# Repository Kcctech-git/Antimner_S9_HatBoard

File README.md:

# Antminer S9 Control Board HAT
## Disclaimer

Following the global mining boom, large numbers of used Antminer S9 control boards have become widely available on secondary markets for as little as $5–30.
These boards, originally built to control cryptocurrency mining equipment, are based on the well-documented Xilinx Zynq-7010 (XC7Z010) SoC and include:

 - Two Arm® Cortex®-A9 processor cores

 - Gigabit Ethernet

 - 512 MB or 1 GB DDR3 RAM

 - 256 Mb SLC NAND flash

 - MicroSD card

 - Exposed PS–PL interface pins, some of which are connected to various peripherals
 
 - Supports Linux and FreeRTOS

Because of their solid hardware design and abundance, these boards make excellent low-cost development platforms for embedded Linux, RTOS, FPGA, or hardware-software co-design experiments — especially when combined with this HAT expansion board.

## Overview

This project is a KiCad-based expansion board (HAT) designed for the Antminer S9 Control Board built around the Xilinx Zynq-7010 (XC7Z010) SoC.
The board extends the original functionality of the control board by adding:

PS-side ULPI USB controller — enabling standard USB host/device connectivity via the Zynq Processing System.

HDMI output interface — connected directly to the Zynq PL (Programmable Logic) fabric for video output or diagnostics.

Breakout header exposing all remaining available PL I/O pins of the Zynq device (except 8 pins used for HDMI).

The goal of this project is to repurpose the Antminer S9 control board into a versatile FPGA development platform, enabling experimentation with Zynq PS/PL subsystems, video output, and general FPGA prototyping.

## Features

 - Compatible with Antminer S9 Zynq-7010 control boards

 - Adds USB ULPI PHY connected to the Zynq PS

 - Adds HDMI TX output using 8 PL pins for TMDS signaling

 - Breaks out all remaining PL I/O to 2.54 mm header

 - Designed in KiCad 9.0 (schematic + PCB files included)

 - Fits within the mechanical envelope of the S9 control board

### This HAT board enables multiple new use cases for the Antminer S9 Control Board:

 - Use as a Zynq FPGA development board with easy access to PL I/O

 - Implement custom video output via HDMI for FPGA or Linux framebuffer

 - Utilize USB host/device support through the PS-side ULPI PHY

 - Experiment with bare-metal or Linux projects using the onboard DDR, flash, and Ethernet

 - Perform reverse engineering, diagnostics, or educational FPGA projects on low-cost S9 boards

## Purpose of the Design

The main goal of this HAT board was to enable the built-in USB 2.0 controller inside the Zynq-7010 Processing System (PS).
Although the Zynq PS includes a native ULPI interface for USB, its signals on the Antminer S9 control board are routed to scattered locations and are not interconnected in a usable way.

This board collects all required ULPI pins from different areas of the control board, aligns their routing lengths, and connects them to a USB PHY (USB3315C).
Because the parallel ULPI bus operates at approximately 60 MHz, and the trace length on the HAT is around 16 cm — close to the reliable signaling limit — special care was taken to maintain consistent line length and impedance.

To minimize signal reflections, 30 Ω series resistors were added on all ULPI data lines.
Testing confirmed that the USB 2.0 interface operates reliably and stably: files larger than 100 MB can be read and written from a USB flash drive without errors.

## Hardware Modifications (Required)

To enable the PS-side ULPI USB interface, a few small modifications are required on the Antminer S9 Zynq-7010 Control Board.
These steps free PS MIO pins previously used by on-board peripherals and provide mechanical clearance for the HAT board.

### Steps

1. Remove Q2 and Q3
These transistors are connected to MIO lines needed for ULPI.
Removing them frees access to: PS_MIO37 and PS_MIO38

2. Wire PS_MIO37 and PS_MIO38 to J11
Solder 60 mm insulated wires from the Q2/Q3 gate pads to PS_MIO37, PS_MIO38

4. Wire PS_MIO39 to J11
Solder a 102 mm insulated wire from the resistor pad (previously tied to control logic) to PS_MIO39

6. Remove capacitors for clearance
Desolder the following mechanically blocking capacitors to allow the HAT board to seat properly C195, C197, C229

7. Connect auxiliary signals to J11 (Aux MIO Connector on HAT)
8. Hook up the freed MIO lines and power signals to the J11 header on the HAT board.
See pinout table below.

9. Provide +12 V to J12 (12 V Pwr on HAT)
10. Connect the +12 V rail from the control board to the J12 input on the HAT.
The HAT generates 5 V and 1.8 V locally for its subsystems.

### J11 (Aux MIO Connector) Pinout
|  Pin	 |  Signal   |	Direction	Notes                                        |
| ----- | --------  | ------------------------------------------------------ |
| 1	    | USB_VDD_IO| (2.5 V)	Power	I/O voltage reference for Zynq PS Bank 1 |
| 2	    | RESET     |	Input	Optional; not used in the reference build        |
| 3     |	PS_MIO39  |	I/O	ULPI signal                                        |
| 4	    | PS_MIO38  |	I/O	ULPI signal                                        |
| 5     |	PS_MIO37  |	I/O	ULPI signal                                        |

### Note: Verify pin orientation according to the silkscreen and schematic before soldering.
Keep wires short (≤ 100 mm) and add strain relief where possible.

### Result:
After completing these modifications, the HAT board’s USB3315C ULPI controller is correctly connected to the Zynq PS USB interface through PS_MIO37–39, with the proper 2.5 V I/O reference and power supplied via J12.

## Bill of Materials (BOM)

| Ref                    | Qty | Value            | Description / Notes                  | Footprint / Link                                                                                                            |
| ---------------------- | --- | ---------------- | ------------------------------------ | --------------------------------------------------------------------------------------------------------------------------- |
| **USB & Power**        |     |                  |                                      |                                                                                                                             |
| IC1                    | 1   | USB3315C-CP-TR   | ULPI USB PHY                         | [Microchip Datasheet](http://ww1.microchip.com/downloads/en/DeviceDoc/3315.pdf)                                             |
| IC2                    | 1   | LM3525M-H        | USB Power Switch                     | [TI Datasheet](https://www.ti.com/product/LM3525)                                                                           |
| J14                    | 1   | USB-C Receptacle | USB2.0 16-pin                        | [USB Type-C Spec](https://www.usb.org/sites/default/files/documents/usb_type-c.zip)                                         |
| J15                    | 1   | 48204-0001       | IO Connector (Molex type)            | [Molex 48204-0001](http://www.molex.com/webdocs/datasheets/pdf/en-us/0482040001_IO_CONNECTORS.pdf)                          |
| Y1                     | 1   | 24 MHz           | ULPI Clock Oscillator                | [Abracon ASV](http://www.abracon.com/Oscillators/ASV.pdf)                                                                   |
| **HDMI Interface**     |     |                  |                                      |                                                                                                                             |
| J13                    | 1   | HDMI Type-A      | Output Connector                     | [Molex 208658-1001](https://www.molex.com/en-us/products/part-detail/2086581001)                                            |
| D1, D6, D7             | 3   | CDDFN10-0524P    | HDMI ESD Protection                  | [Bourns CDDFN10-0524P](https://www.bourns.com/docs/Product-Datasheets/CDDFN10-0524P.pdf)                                    |
| **Voltage Regulation** |     |                  |                                      |                                                                                                                             |
| U1                     | 1   | L7805            | 5 V Linear Regulator                 | [ST L7805](https://www.st.com/resource/en/datasheet/l78.pdf)      |
| U2                     | 1   | LM1117DT-1.8     | 1.8 V Regulator                      | [TI LM1117](http://www.ti.com/lit/ds/symlink/lm1117.pdf)                                                                    |
| **Connectors**         |     |                  |                                      |                                                                                                                             |
| J1–J9                  | 9   | Conn_02x09       | PL / GPIO Headers (2 mm pitch)       | —                                                                                                                           |
| J11                    | 1   | Aux_mio_conn     | 1×5 Header 2.54 mm                   | —                                                                                                                           |
| J12                    | 1   | 12 V Pwr         | 2×2 Socket 2.54 mm                   | —                                                                                                                           |
| J16                    | 1   | PL_conn          | 1×37 Header 2.54 mm                  | —                                                                                                                           |
| **Passive Components** |     |                  |                                      |                                                                                                                             |
| C1                     | 1   | 47 µF 25 V       | Bulk decoupling                      | 1206                                                                                                                        |
| C2                     | 1   | 100 µF 10 V      | Bulk decoupling                      | 1206                                                                                                                        |
| C3                     | 1   | 100 nF           | Decoupling                           | 1206                                                                                                                        |
| C4                     | 1   | 1 nF             | Filter                               | 1206                                                                                                                        |
| C5, C6, C13, C23, C25  | 5   | 0.1 µF           | Bypass capacitors                    | 0805                                                                                                                        |
| C7                     | 1   | 100 µF           | Bulk capacitor                       | 1210                                                                                                                        |
| C8                     | 1   | 1 nF             | Filter                               | 1206                                                                                                                        |
| C14, C24               | 2   | 10 µF            | Local decoupling                     | 1206                                                                                                                        |
| R1                     | 1   | 1 MΩ             | Pull-down                            | 0805                                                                                                                        |
| R2                     | 1   | 820 Ω            | LED limiter                          | 0805                                                                                                                        |
| R3, R20                | 2   | 2 kΩ             | General pull-up                      | 0805                                                                                                                        |
| R4                     | 1   | 4.7 kΩ           | I²C pull-up                          | 0805                                                                                                                        |
| R5                     | 1   | 8.06 kΩ          | Divider                              | 0805                                                                                                                        |
| R6–R19                 | 11  | 30 Ω             | HDMI series termination              | 0805                                                                                                                        |
| R21                    | 1   | 1 MΩ             | General pull-down                    | 0805                                                                                                                        |
| RN1, RN2               | 2   | TC164-FR-0749R9L | 49.9 Ω resistor network (4×)         | [Yageo Datasheet](https://www.yageo.com/upload/media/product/productsearch/datasheet/rchip/PYu-YC_TC_group_51_RoHS_L_9.pdf) |
| D2, D8                 | 2   | LED              | Status indicators                    | Any 1206/1210 Leds                                                                                                                        |
| D4                     | 1   | 1N5822           | Schottky diode                       | [Vishay 1N5822](http://www.vishay.com/docs/88526/1n5820.pdf)                                                                |
| **Test Points**        |     |                  |                                      |                                                                                                                             |
| TP1–TP6                | 6   | —                | CEC, SCL, SDA, HPD, UTILITY, 5V_HDMI | TestPoint Ø1.5 mm                                                                                                           |

## Known Limitations

HDMI interface uses AC-coupled LVCMOS-TMDS signaling (non-standard but functional).

Voltage compatibility of some PL banks depends on existing S9 circuitry — verify I/O standards before connecting.

Power is drawn directly from the S9 board (3.3 V and 12 V rails).

## License

Licensed under CERN Open Hardware Licence v2 - Permissive (CERN-OHL-P)
SPDX-License-Identifier: CERN-OHL-P-2.0

Full license text:
https://ohwr.org/cern_ohl_p_v2.txt

## Credits

Designed by Kanstantsin Salamiyuk

Created to extend and repurpose the Antminer S9 Zynq-7010 control board as an open FPGA development platform.
KiCad design files and documentation are provided for educational and experimental use.

## Disclaimer

This project is not affiliated with or endorsed by Bitmain Technologies.
All hardware modifications and usage are performed at your own risk.
Improper connections may damage the control board or FPGA.

**Tags:** `FPGA` `Zynq-7010` `Antminer S9` `Embedded Linux` `ULPI` `HDMI` `Open Hardware`

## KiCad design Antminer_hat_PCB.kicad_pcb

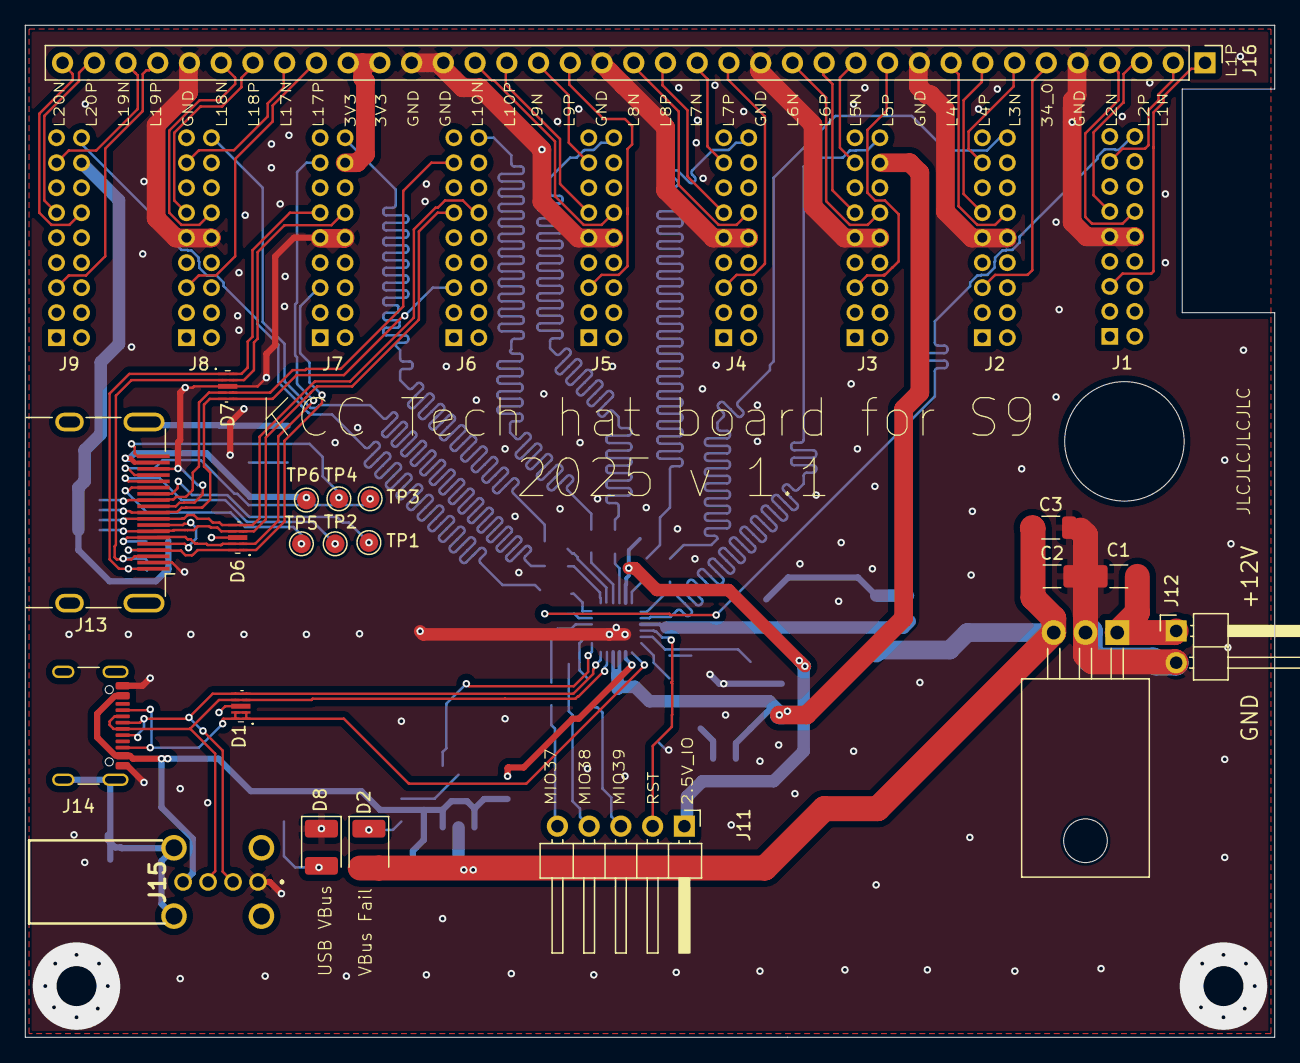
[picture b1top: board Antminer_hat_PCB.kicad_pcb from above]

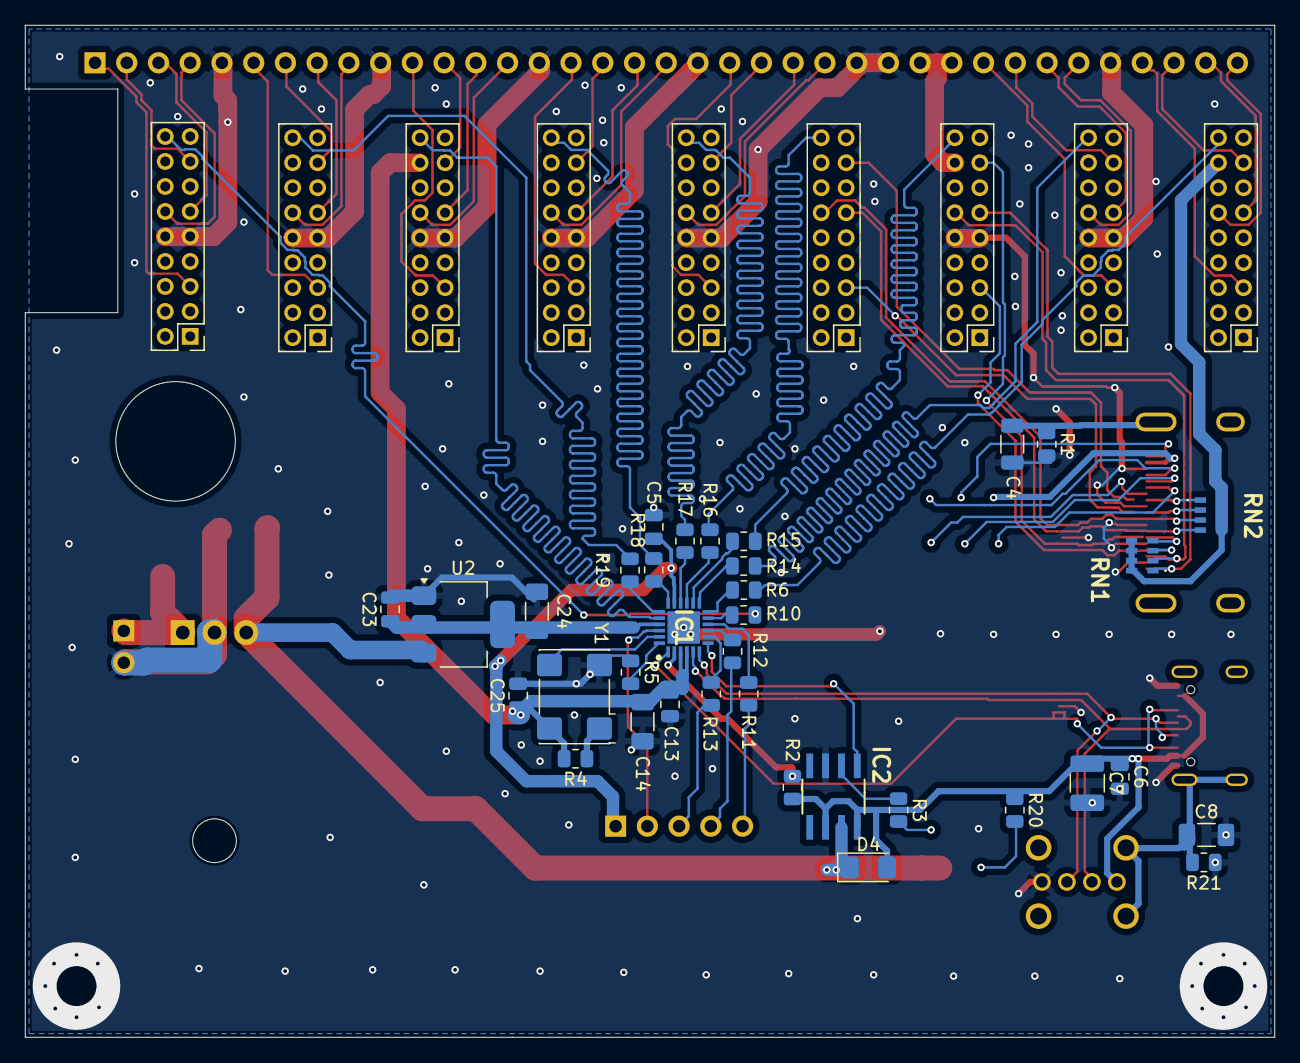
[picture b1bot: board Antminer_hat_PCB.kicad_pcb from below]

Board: 2 copper layers, 100.0 x 81.0 mm, 65 parts (44 on the bottom side), 86 nets.

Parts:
C1: 47uf 25v; C_1206_3216Metric
C2: 100 uf 10v; C_1206_3216Metric
C3: 100n; C_1206_3216Metric
C4: 1n; C_1206_3216Metric
C5, C6, C13, C23, C25: 0.1uf; C_0805_2012Metric
C7: 100uf; C_1210_3225Metric_Pad1.33x2.70mm_HandSolder
C8: 1n; C_1206_3216Metric_Pad1.33x1.80mm_HandSolder
C14, C24: 10uf; C_1206_3216Metric_Pad1.33x1.80mm_HandSolder
D1, D6, D7: CDDFN10-0524P; CDDFN100524P
D2, D8: LED; LED_1210_3225Metric_Pad1.42x2.65mm_HandSolder
D4: 1N5822; D_1206_3216Metric_Pad1.42x1.75mm_HandSolder
IC1: USB3315C-CP-TR; QFN50P400X400X100-25N-D
IC2: LM3525M-H; SOIC127P620X175-8N
J1, J2, J3, J4, J5, J6, J7, J8, J9: Conn_02x09_Odd_Even; PinHeader_2x09_P2.00mm_Vertical
J11: Aux_mio_conn; PinHeader_1x05_P2.54mm_Horizontal
J12: 12v Pwr; PinHeader_1x02_P2.54mm_Horizontal
J13: HDMI_A; HDMI_A_Molex_208658-1001_Horizontal
J14: USB_C_Receptacle_USB2.0_16P; USB_C_Receptacle_GCT_USB4105-xx-A_16P_TopMnt_Horizontal
J15: 48204-0001 China; 482040001
J16: PL_conn; PinHeader_1x37_P2.54mm_Vertical
R1: 1m; R_0805_2012Metric
R2: 820; R_0805_2012Metric
R3, R20: 2k; R_0805_2012Metric
R4: 4k7; R_0805_2012Metric
R5: 8k06; R_0805_2012Metric
R6, R10, R11, R12, R13, R14, R15, R16, R17, R18, R19: 30; R_0805_2012Metric
R21: 1M; R_0805_2012Metric
RN1, RN2: TC164-FR-0749R9L; TC164FR0749R9L
TP1: CEC; TestPoint_Pad_D1.5mm
TP2: SCL; TestPoint_Pad_D1.5mm
TP3: SDA; TestPoint_Pad_D1.5mm
TP4: HPD; TestPoint_Pad_D1.5mm
TP5: UTILITY; TestPoint_Pad_D1.5mm
TP6: 5V_HDMI; TestPoint_Pad_D1.5mm
U1: L7805; TO-220-3_Horizontal_TabDown
U2: LM1117DT-1.8; SOT-223-3_TabPin2
Y1: 24Mhz; Oscillator_SMD_Abracon_ASV-4Pin_7.0x5.1mm

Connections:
2.5VCC_IO: C5.1, IC1.17 (VDDIO), J11.1
+1.8V: C23.1, C24.1, IC1.21 (VDD1.8), U2.2 (VO)
+3.3V: C13.1, C14.1, C25.1, IC1.3 (VBAT), IC1.4 (VDD3.3), J3.16, J7.16, J9.16, J16.27, J16.28, R4.2, RN1.5, RN1.6, RN1.7, RN1.8, RN2.5, RN2.6, RN2.7, RN2.8, Y1.4 (Vdd)
+5V: C2.1, C3.1, D2.2 (A), D4.1 (K), IC2.7 (IN), U1.3 (OUT), U2.3 (VI)
+12V: C1.1, J12.1, U1.1 (IN)
/BANK34_0_PLUG2: J2.5, J16.6
/BANK34_L1N_RST1: J1.15, J16.2
/BANK34_L1P_PLUG1: J1.5, J16.1
/BANK34_L2N_RXD1: J1.12, J16.4
/BANK34_L2P_TXD1: J1.11, J16.3
/BANK34_L3N_RST2: J2.15, J16.7
/BANK34_L4N_RXD2: J2.12, J16.9
/BANK34_L4P_TXD2: J2.11, J16.8
/BANK34_L5N_RST3: J3.15, J16.12
/BANK34_L5P_PLUG3: J3.5, J16.11
/BANK34_L6N_RXD3: J3.12, J16.14
/BANK34_L6P_TXD3: J3.11, J16.13
/BANK34_L7N_RST4: J4.15, J16.17
/BANK34_L7P_PLUG4: J4.5, J16.16
/BANK34_L8N_RXD4: J4.12, J16.19
/BANK34_L8P_TXD4: J4.11, J16.18
/BANK34_L9N_RST5: J5.15, J16.22
/BANK34_L9P_PLUG5: J5.5, J16.21
/BANK34_L10N_RXD5: J5.12, J16.24
/BANK34_L10P_TXD5: J5.11, J16.23
/BANK34_L11N_RST6: D7.4 (LINE-3), D7.7 (NC_2), J6.15, J13.12 (CK-), RN2.1
/BANK34_L11P_PLUG6: D7.5 (LINE-4), D7.6 (NC_1), J6.5, J13.10 (CK+), RN2.2
/BANK34_L12N_RXD6: D6.5 (LINE-4), D6.6 (NC_1), J6.12, J13.9 (D0-), RN2.3
/BANK34_L12P_TXD6: D6.4 (LINE-3), D6.7 (NC_2), J6.11, J13.7 (D0+), RN2.4
/BANK34_L15N_RST7: D6.2 (LINE-2), D6.9 (NC_3), J7.15, J13.6 (D1-), RN1.4
/BANK34_L15P__PLUG7: D6.1 (LINE_-1), D6.10 (NC_4), J7.5, J13.4 (D1+), RN1.3
/BANK34_L16N_RXD7: D7.2 (LINE-2), D7.9 (NC_3), J7.12, J13.3 (D2-), RN1.2
/BANK34_L16P_TXD7: D7.1 (LINE_-1), D7.10 (NC_4), J7.11, J13.1 (D2+), RN1.1
/BANK34_L17N_RST8: J8.15, J16.30
/BANK34_L17P_PLUG8: J8.5, J16.29
/BANK34_L18N_RXD8: J8.12, J16.32
/BANK34_L18P_TXD8: J8.11, J16.31
/BANK34_L19N_RST9: J9.15, J16.35
/BANK34_L19P_PLUG9: J9.5, J16.34
/BANK34_L20N_RXD9: J9.12, J16.37
/BANK34_L20P_TXD9: J9.11, J16.36
/Usb connection/USB_D+: D1.5 (LINE-4), D1.6 (NC_1), IC1.6 (DP), J14.A6 (D+), J14.B6 (D+), J15.2 (D+)
/Usb connection/USB_D-: D1.4 (LINE-3), D1.7 (NC_2), IC1.5 (DM), J14.A7 (D-), J14.B7 (D-), J15.3 (D-)
/Usb connection/V_BUS: C6.1, C7.1, D4.2 (A), IC2.6 (OUT_2), IC2.8 (OUT), J14.A4 (VBUS), J14.A9 (VBUS), J14.B4 (VBUS), J14.B9 (VBUS), J15.4 (V_BUS), R2.1, R20.1
CLK: J9.18, R6.2
DATA0: J5.18, R17.2
DATA1: J6.18, R16.2
DATA2: J7.18, R15.2
DATA3: J8.18, R14.2
DATA4: J1.18, R10.2
DATA5: J11.5, R11.2
DATA6: J11.4, R12.2
DATA7: J11.3, R13.2
DIR: J2.18, R19.2
GND: C1.2, C2.2, C3.2, C4.2, C5.2, C6.2, C7.2, C8.2, C13.2, C14.2, C23.2, C24.2, C25.2, D1.3 (GND), D6.3 (GND), D7.3 (GND), D8.1 (K), IC1.25 (GND), IC2.3 (GND), J1.9, J1.10, J2.9, J2.10, J3.9, J3.10, J4.9, J4.10, J5.9, J5.10, J7.9, J7.10, J8.9, J8.10, J12.2, J13.2 (D2S), J13.5 (D1S), J13.8 (D0S), J13.11 (CKS), J13.17 (GND), J14.A1 (GND), J14.A12 (GND), J14.B1 (GND), J14.B12 (GND), J15.1 (GND), J16.5, J16.10, J16.15, J16.20, J16.25, J16.26, J16.33, R1.2, R5.1, R21.1, U1.2 (GND), U2.1 (GND), Y1.2 (GND)
NXT: J4.18, R18.2
unnamed: C4.1, J13.SH, R1.1
unnamed: D1.1 (LINE_-1), D1.2 (LINE-2), D1.9 (NC_3), D1.10 (NC_4), IC1.1 (ID), J14.A5 (CC1), J14.B5 (CC2)
unnamed: D2.1 (K), R3.2
unnamed: D8.2 (A), R20.2
unnamed: IC1.12 (CLKOUT), R6.1
unnamed: IC1.7 (CPEN), IC2.1 (EN)
unnamed: IC1.16 (DATA0), R17.1
unnamed: IC1.15 (DATA1), R16.1
unnamed: IC1.14 (DATA2), R15.1
unnamed: IC1.13 (DATA3), R14.1
unnamed: IC1.11 (DATA4), R10.1
unnamed: IC1.10 (DATA5), R11.1
unnamed: IC1.9 (DATA6), R12.1
unnamed: IC1.8 (DATA7), R13.1
unnamed: IC1.19 (DIR), R19.1
unnamed: IC1.18 (NXT), R18.1
unnamed: IC1.24 (RBIAS), R5.2
unnamed: IC1.23 (REFCLK), Y1.3 (OUT)
unnamed: IC1.2 (VBUS), R2.2
unnamed: IC2.2 (FLAG), R3.1
unnamed: J13.18 (+5V), TP6.1
unnamed: J13.13 (CEC), TP1.1
unnamed: J13.19 (HPD), TP4.1
unnamed: J13.15 (SCL), TP2.1
unnamed: J13.16 (SDA), TP3.1
unnamed: J13.14 (UTILITY), TP5.1
unnamed: C8.1, J14.S1 (SHIELD), J15.5 (Shield), J15.6 (Shield), J15.7 (Shield), J15.8 (Shield), R21.2
unnamed: R4.1, Y1.1 (EN)
RST: IC1.22 (RESETB), J11.2
STP: IC1.20 (STP), J3.18

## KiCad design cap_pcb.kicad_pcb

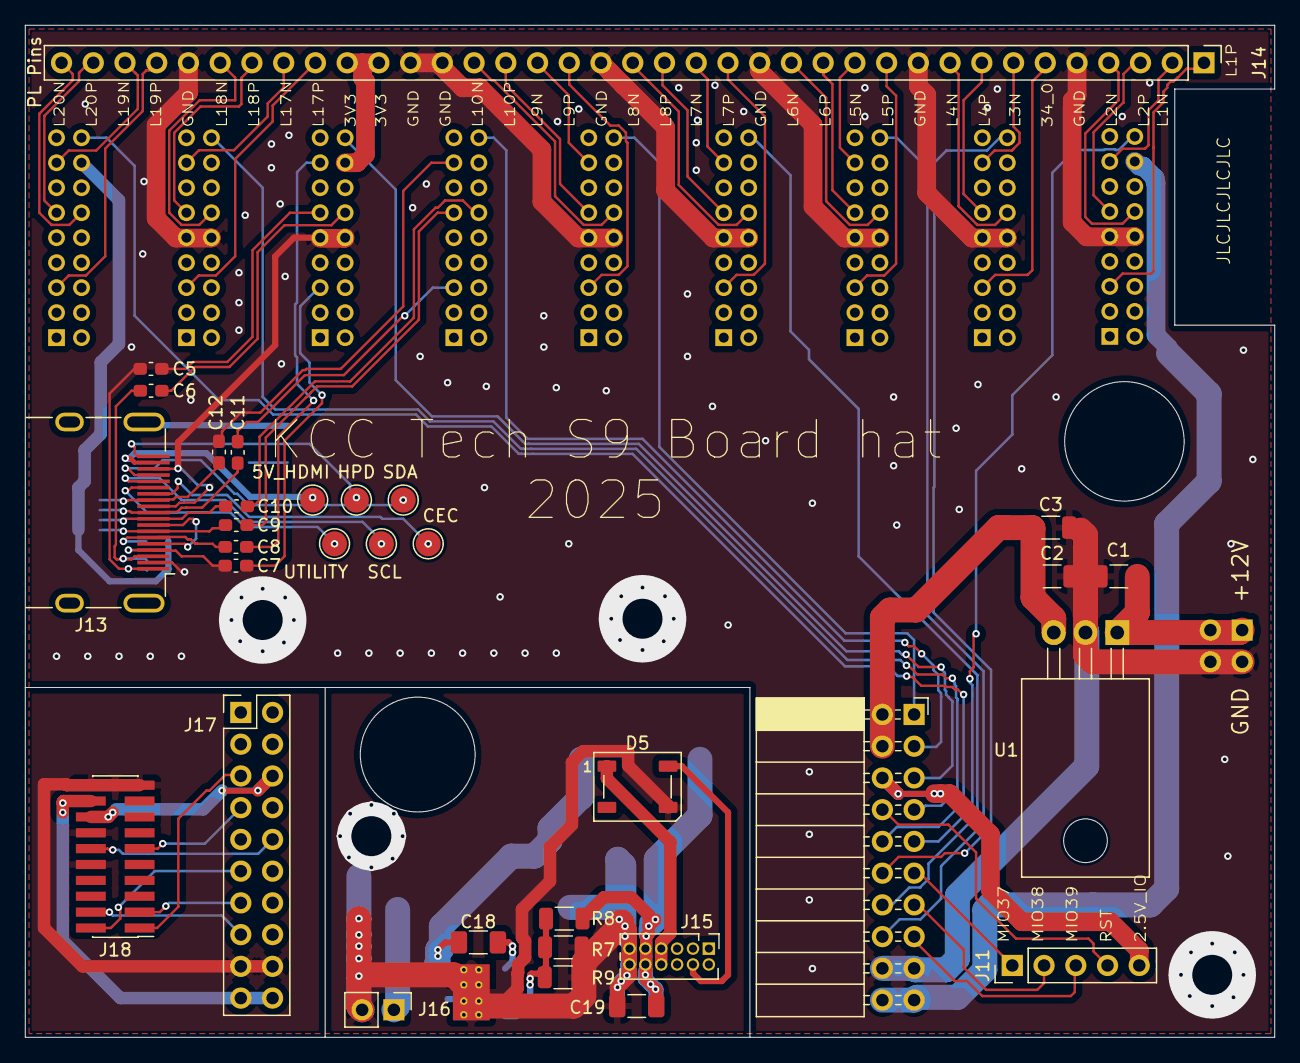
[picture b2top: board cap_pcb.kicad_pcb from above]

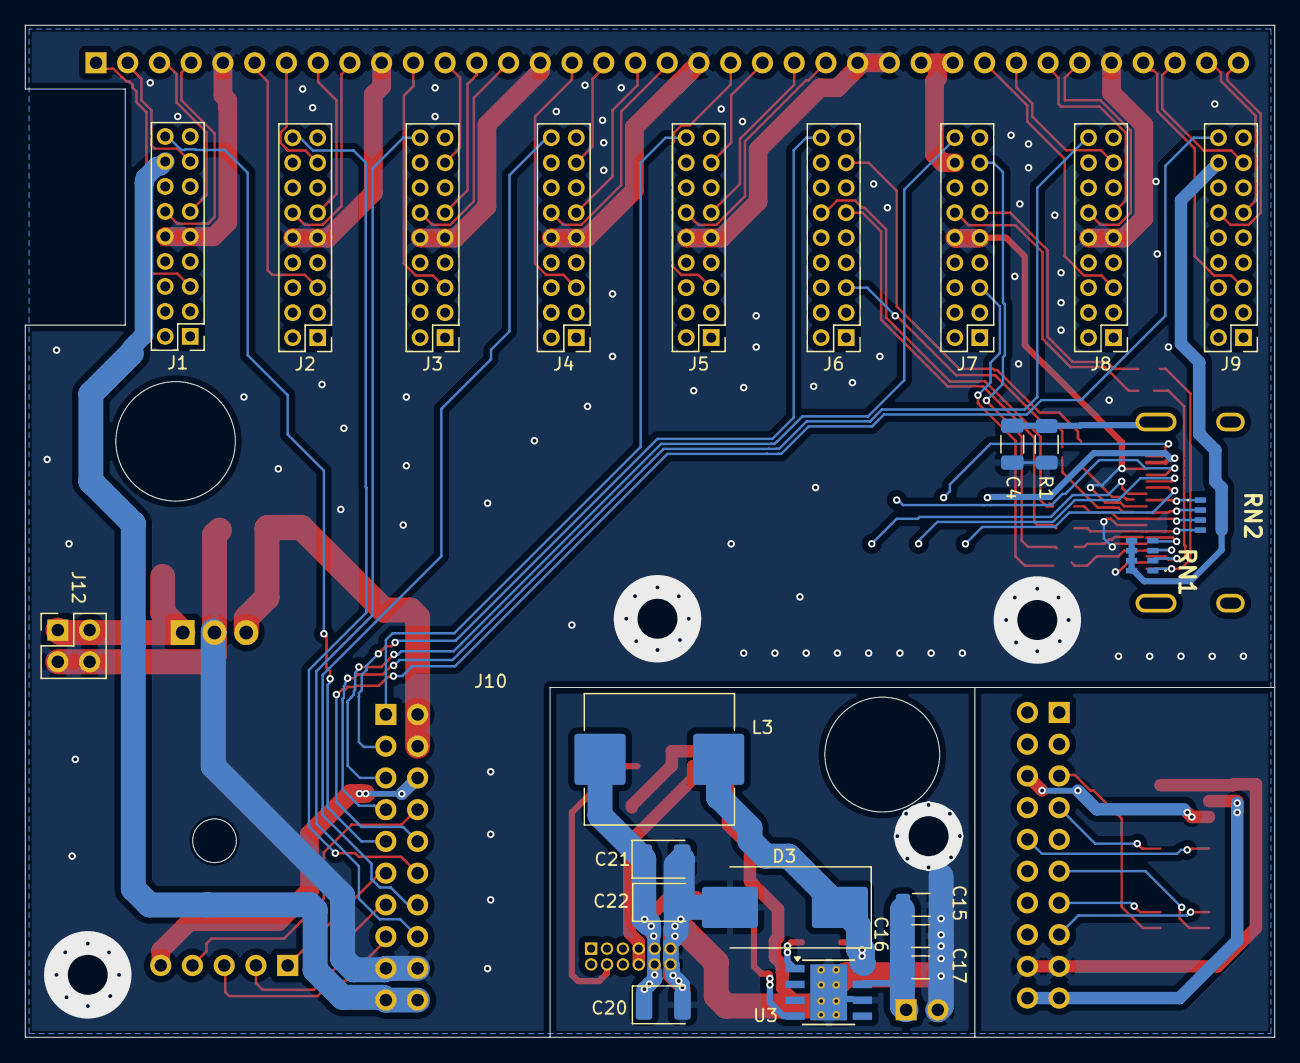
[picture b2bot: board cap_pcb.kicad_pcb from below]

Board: 2 copper layers, 100.0 x 81.0 mm, 55 parts (23 on the bottom side), 84 nets.

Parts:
C1: 47uf 25v; C_1206_3216Metric
C2: 100 uf 10v; C_1206_3216Metric
C3: 100n; C_1206_3216Metric
C4: 1n; C_1206_3216Metric
C5, C6, C7, C8, C9, C10, C11, C12: 100n; C_0603_1608Metric_Pad1.08x0.95mm_HandSolder
C15, C16, C17: 22uf 25v; C_1206_3216Metric
C18: 10n; C_1206_3216Metric_Pad1.33x1.80mm_HandSolder
C19: 10uf 50v; C_1206_3216Metric_Pad1.33x1.80mm_HandSolder
C20, C21, C22: 47uf 10v; CP_EIA-3528-12_Kemet-T
D3: SS54; D_SMC_Handsoldering
D5: WS2812B-B/T; LED_WS2812B_PLCC4_5.0x5.0mm_P3.2mm
J1, J2, J3, J4, J5, J6, J7, J8, J9: Conn_02x09_Odd_Even; PinHeader_2x09_P2.00mm_Vertical
J10: USB Expansion board; PinSocket_2x10_P2.54mm_Horizontal
J11: Aux_mio_conn; PinHeader_1x05_P2.54mm_Vertical
J12: 12v Pwr; PinSocket_2x02_P2.54mm_Vertical
J13: HDMI_A; HDMI_A_Molex_208658-1001_Horizontal
J14: PL Pins; PinHeader_1x37_P2.54mm_Vertical
J15: Conn_02x06 Extension; PinHeader_2x06_P1.27mm_Vertical
J16: Conn_01x02_Pin; PinHeader_1x02_P2.54mm_Vertical
J17: SD_MODULE_CONN; PinHeader_2x10_P2.54mm_Vertical
J18: EMMC_CONN; PinHeader_2x10_P1.27mm_Vertical_SMD
L3: 22uh 4A; L_Sunlord_MWSA1003S
R1: 1m; R_1206_3216Metric
R7: 10k; R_1206_3216Metric
R8: 3k3; R_1206_3216Metric
R9: 150k; R_1206_3216Metric
RN1, RN2: TC164-FR-0749R9L; TC164FR0749R9L
TP1: CEC; TestPoint_Pad_D2.0mm
TP2: SCL; TestPoint_Pad_D2.0mm
TP3: SDA; TestPoint_Pad_D2.0mm
TP4: HPD; TestPoint_Pad_D2.0mm
TP5: UTILITY; TestPoint_Pad_D2.0mm
TP6: 5V_HDMI; TestPoint_Pad_D2.0mm
U1: L7805; TO-220-3_Horizontal_TabDown
U3: TPS5430DDA; TI_SO-PowerPAD-8_ThermalVias

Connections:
+3.3V: D5.1 (VDD), J15.7, J15.8
+5.0v: C19.1, C20.1, C21.1, C22.1, J15.9, J15.10, L3.2, R7.1
+5V: C2.1, C3.1, J10.2, J10.4, U1.3 (OUT)
+12V: C1.1, J12.1, J12.3, U1.1 (IN)
/2.5VCC_IO: J10.6, J11.5
/3.3V: J1.16, J7.16, J8.16, J9.16, J10.19, J10.20, J14.27, J14.28, RN1.5, RN1.6, RN1.7, RN1.8, RN2.5, RN2.6, RN2.7, RN2.8
/BANK34_0_PLUG2: J2.5, J14.6
/BANK34_L1N_RST1: J1.15, J14.2
/BANK34_L1P_PLUG1: J1.5, J14.1
/BANK34_L2N_RXD1: J1.12, J14.4
/BANK34_L2P_TXD1: J1.11, J14.3
/BANK34_L3N_RST2: J2.15, J14.7
/BANK34_L4N_RXD2: J2.12, J14.9
/BANK34_L4P_TXD2: J2.11, J14.8
/BANK34_L5N_RST3: J3.15, J14.12
/BANK34_L5P_PLUG3: J3.5, J14.11
/BANK34_L6N_RXD3: J3.12, J14.14
/BANK34_L6P_TXD3: J3.11, J14.13
/BANK34_L7N_RST4: J4.15, J14.17
/BANK34_L7P_PLUG4: J4.5, J14.16
/BANK34_L8N_RXD4: J4.12, J14.19
/BANK34_L8P_TXD4: J4.11, J14.18
/BANK34_L9N_RST5: J5.15, J14.22
/BANK34_L9P_PLUG5: J5.5, J14.21
/BANK34_L10N_RXD5: J5.12, J14.24
/BANK34_L10P_TXD5: J5.11, J14.23
/BANK34_L11N_RST6: C12.1, J6.15
/BANK34_L11P_PLUG6: C11.1, J6.5
/BANK34_L12N_RXD6: C10.1, J6.12
/BANK34_L12P_TXD6: C9.1, J6.11
/BANK34_L15N_RST7: C8.1, J7.15
/BANK34_L15P__PLUG7: C7.1, J7.5
/BANK34_L16N_RXD7: C6.1, J7.12
/BANK34_L16P_TXD7: C5.1, J7.11
/BANK34_L17N_RST8: J8.15, J14.30
/BANK34_L17P_PLUG8: J8.5, J14.29
/BANK34_L18N_RXD8: J8.12, J14.32
/BANK34_L18P_TXD8: J8.11, J14.31
/BANK34_L19N_RST9: J9.15, J14.35
/BANK34_L19P_PLUG9: J9.5, J14.34
/BANK34_L20N_RXD9: J9.12, J14.37
/BANK34_L20P_TXD9: J9.11, J14.36
/CLK: J9.18, J10.10
/DATA0: J5.18, J10.1
/DATA1: J6.18, J10.3
/DATA2: J7.18, J10.5
/DATA3: J8.18, J10.7
/DATA4: J1.18, J10.9
/DATA5: J10.11, J11.1
/DATA6: J10.13, J11.2
/DATA7: J10.15, J11.3
/DIR: J2.18, J10.12
/Modules/+VIN: C15.1, C16.1, C17.1, J16.1, U3.7 (VIN)
/Modules/SD_D0: J17.5, J18.1
/Modules/SD_D1: J17.11, J18.2
/Modules/SD_D2: J17.13, J18.3
/Modules/SD_D3: J17.15, J18.4
/Modules/SD­_3.3V: J17.19, J17.20, J18.18
/Modules/SD­_CLK: J17.10, J18.12
/Modules/SD­_VCC_IO: J17.6, J18.16
/Modules/SD­­_CMD: J17.7, J18.11
/NXT: J4.18, J10.14
/PS_MIO30: J3.18, J10.16
/RST: J10.8, J11.4
Ext_IO_14: D5.4 (DIN), J15.4
GND: C1.2, C2.2, C3.2, C4.2, C15.2, C16.2, C17.2, C19.2, C20.2, C21.2, C22.2, D3.2 (A), D5.3 (VSS), J1.9, J1.10, J2.9, J2.10, J3.9, J3.10, J4.9, J4.10, J5.9, J5.10, J7.9, J7.10, J8.9, J8.10, J10.17, J10.18, J12.2, J12.4, J13.2 (D2S), J13.5 (D1S), J13.8 (D0S), J13.11 (CKS), J13.17 (GND), J14.5, J14.10, J14.15, J14.20, J14.25, J14.26, J14.33, J15.11, J15.12, J16.2, J17.17, J17.18, J18.10, J18.14, J18.19, J18.20, R1.2, R8.2, R9.2, U1.2 (GND), U3.6 (GND), U3.9 (GNDPAD)
unnamed: C4.1, J13.SH, R1.1
unnamed: C18.2, D3.1 (K), L3.1, U3.8 (PH)
unnamed: J13.18 (+5V), TP6.1
unnamed: J13.13 (CEC), TP1.1
unnamed: C11.2, J13.10 (CK+), RN2.2
unnamed: C12.2, J13.12 (CK-), RN2.1
unnamed: C9.2, J13.7 (D0+), RN2.4
unnamed: C10.2, J13.9 (D0-), RN2.3
unnamed: C7.2, J13.4 (D1+), RN1.3
unnamed: C8.2, J13.6 (D1-), RN1.4
unnamed: C5.2, J13.1 (D2+), RN1.1
unnamed: C6.2, J13.3 (D2-), RN1.2
unnamed: J13.19 (HPD), TP4.1
unnamed: J13.15 (SCL), TP2.1
unnamed: J13.16 (SDA), TP3.1
unnamed: J13.14 (UTILITY), TP5.1
unnamed: C18.1, U3.1 (BOOT)
unnamed: R7.2, R8.1, R9.1, U3.4 (VSENSE)

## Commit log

2025-06-23 - Initial commit of PCB
2025-06-24 - Added capacitors on HDMI TDMS lines
2025-10-14 Updates for version 1.1: - Project named as Antminer_hat_pcb - Added USB3315 Phy on board - Removed ULPI connector - Optimized HDMI wiring - Other updates
2025-10-14 Created README.md
2025-10-15 - Added board pictures
2025-10-15 - Updated schematic to use correct type of external connectors
2025-10-15 Update README.md
    - Added pictures to readme
    - Updated pinout for J11 according to schematics modifications
2025-10-15 - Added connection points picture
2025-10-15 - Added picture with ULPI signals routing
2025-10-15 - Routing picture is updated
2025-10-15 Clarify purpose and features in README
    - Updated the README to clarify the purpose and features of the Antminer S9 Control Board HAT. Added details about hardware modifications and improved formatting for better readability.
